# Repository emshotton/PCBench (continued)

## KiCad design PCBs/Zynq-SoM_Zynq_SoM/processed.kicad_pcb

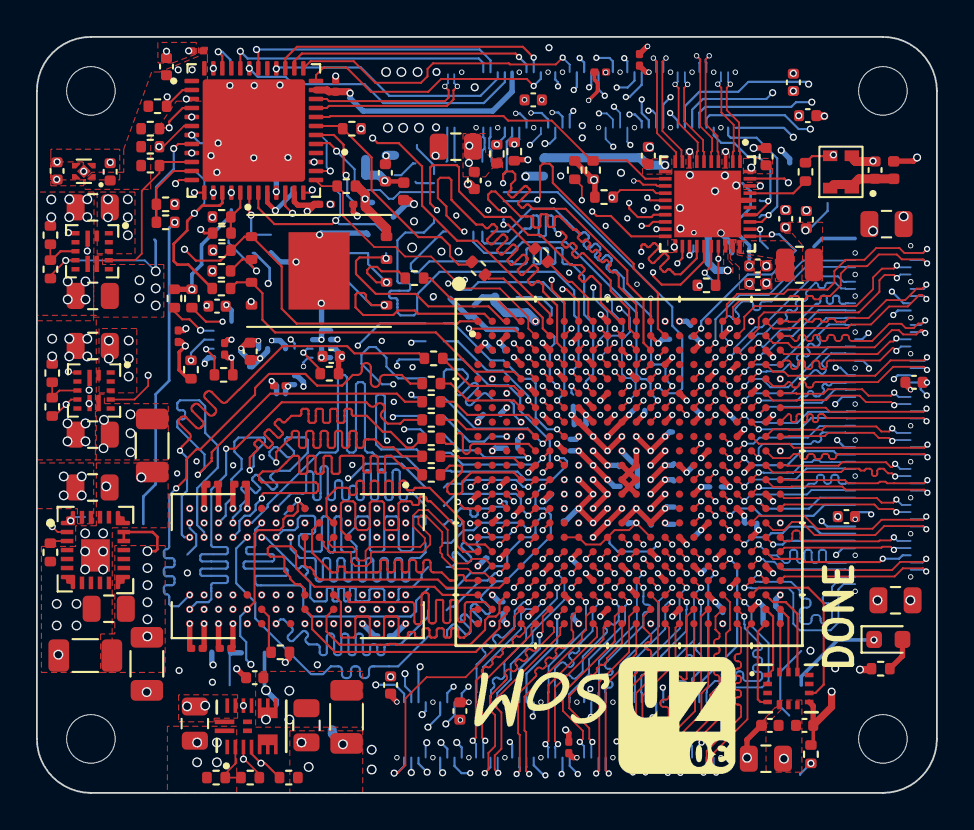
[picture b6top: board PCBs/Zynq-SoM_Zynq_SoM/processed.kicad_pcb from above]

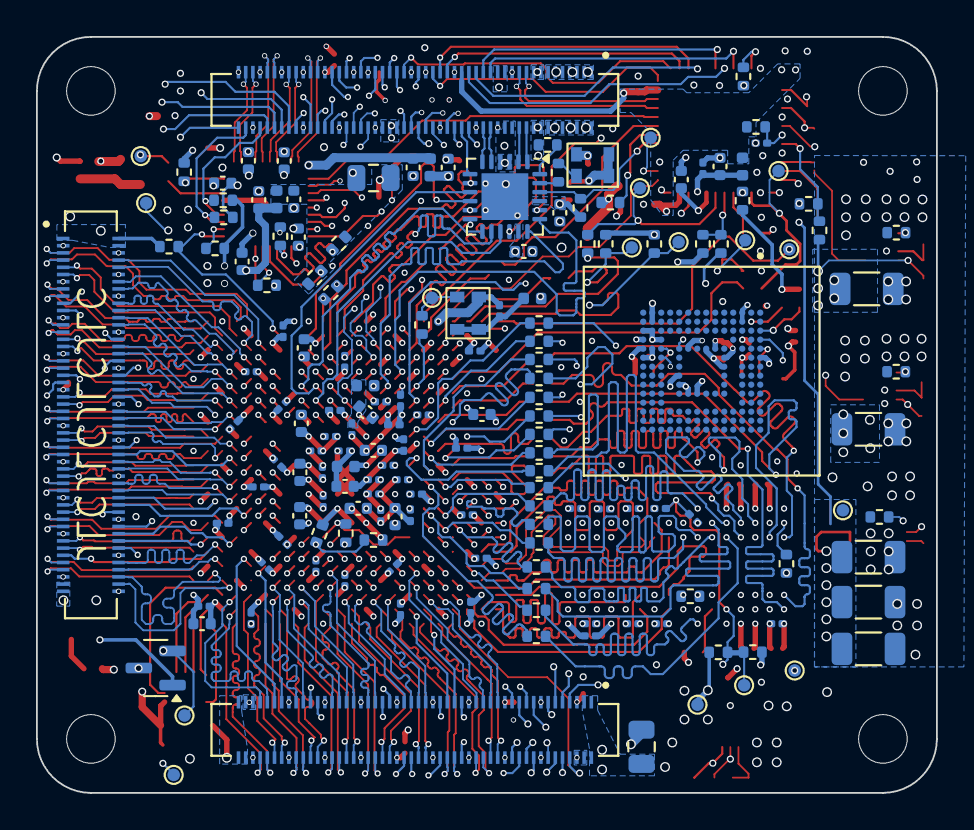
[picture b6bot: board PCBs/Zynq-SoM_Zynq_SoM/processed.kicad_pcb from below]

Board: 8 copper layers, 50.0 x 42.0 mm, 287 parts (166 on the bottom side), 393 nets.

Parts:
C1, C7, C8, C9, C10, C11, C12, C15, C32, C34, C36, C38, C40, C44, C45, C52, C57, C59, C66, C70, C71, C77, C78, C79, C87, C88, C95, C97, C103, C123, C128, C129, C139, C141: 4u7; C_0402_1005Metric
C2, C3, C4, C5, C6, C16, C17, C18, C19, C20, C21, C22, C138, C142: 100n; C_0402_1005Metric
C13, C23, C33, C35, C37, C39, C41, C43, C46, C47, C48, C50, C53, C54, C55, C56, C61, C62, C67, C69, C72, C76, C80, C81, C82, C83, C84, C85, C89, C90, C91, C92, C94, C98, C99, C100, C101, C102, C107, C108, C112, C114, C130, C131, C132, C133, C134, C135, C136, C137: 470n; C_0201_0603Metric
C24, C27, C28, C29, C31, C49, C73, C74, C75, C86, C127: 47u; C_0805_2012Metric
C25, C26, C30: 22u; C_0805_2012Metric
C42, C51, C58, C60, C63, C64, C68, C93, C96: 100u; C_1206_3216Metric
C65: 10u; C_0402_1005Metric
C104, C105, C106, C109, C110, C111, C113, C118, C119, C120, C121, C122, C124, C125, C126: 47n; C_0201_0603Metric
D2: LED_Small; LED_0603_1608Metric
H1, H2, H3, H4: MountingHole; MountingHole_2.7mm_M2.5_ISO14580_MOD
J1, J2, J3: DF40C-100DS-0.4V_51; HRS_DF40C-100DS-0.4V_51_
L1: 3u3; L_0806_2.0x1.6mm
L2, L3, L4, L6, L7, L8, L9: 120R; L_0402_1005Metric
L5: 600@100MHz; L_0402_1005Metric
Q3: NMOS; SOT-23
R1, R5, R6, R13, R15, R39, R40, R41, R42, R43, R44, R74, R75, R76, R77, R86, R87, R88, R89, R90, R92, R93, R94, R97, R100: 10k; R_0402_1005Metric
R2, R20, R21, R22, R49, R51, R52, R53, R54, R55, R56, R57, R58, R59, R60, R61, R62, R63, R64, R65, R66, R67, R68, R69, R70, R71, R72, R73, R95, R96: 22R; R_0402_1005Metric
R3, R4, R14: 1k5; R_0402_1005Metric
R7, R8, R9, R10, R11, R12, R17, R18, R19, R48, R98, R99: 4k7; R_0402_1005Metric
R16: 2k49; R_0402_1005Metric
R23, R27, R28, R29, R30, R31, R32, R35, R36, R78, R79, R80, R81, R82, R83, R84, R85: 100k; R_0402_1005Metric
R24: 8k06; R_0402_1005Metric
R25: 28k7; R_0402_1005Metric
R26, R33, R37: 200k; R_0402_1005Metric
R34: 44k2; R_0402_1005Metric
R38: 160k; R_0402_1005Metric
R45: 240R; R_0402_1005Metric
R46, R47: 100R; R_0201_0603Metric
R50: 100R; R_0402_1005Metric
R91: 330; R_0402_1005Metric
TP1, TP2, TP3, TP4, TP5, TP6, TP7, TP8, TP9, TP10, TP11, TP12, TP13, TP14, TP15, TP16: TestPoint; TestPoint_Pad_D0.7mm
U1: MT41K256M16TW-107_P; BGA96C80P9X16_1400X800X120
U2: XC7Z020-CLG484; CLG484_XIL-L_new
U3: RTL8211F; RTL8211F-CG_RTK-L
U4, U6: MPM3834
U5: USB3318; QFN-24-1EP_4x4mm_P0.5mm_EP2.6x2.6mm
U7: IS21ES08G; BGA153N50P14X14_1150X1300X100
U8: TPSM82864; B0QFN_RDJ
U9: STM32G431CBUx; STM32G431CBU6
U10: MPM3822; QFN_2p5x3p5x1p6_MNP
U11: W25Q128JVS; WSON-8-1EP_8x6mm_P1.27mm_EP3.4x4.3mm
U13: TPS7A20; TLV707
U14: BMI323; BMI323_BOS
X1: ASCO; Oscillator_SMD_Kyocera_4PIN_2.0x1.6mm
X2: ASE-xxxMHz; Oscillator_SMD_Kyocera_4PIN_2.0x1.6mm
X3: CMOS_OSC; Oscillator_SMD_Kyocera_4PIN_2.0x1.6mm

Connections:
1V0_EN: R27.1, U8.1 (EN), U9.5 (PF0)
1V0_PG: R28.2, U8.2 (PG), U9.2 (PC13)
1V8_EN: R30.1, U4.3 (EN), U9.47 (PB9)
1V8_PG: R29.2, U4.11 (PG), U9.4 (PC15)
1V35_EN: R35.1, U9.9 (PA1), U10.4 (EN)
1V35_PG: R36.2, U9.6 (PF1), U10.12 (PG)
3V3_EN: R31.1, U6.3 (EN), U9.3 (PC14)
3V3_PG: R32.2, U6.11 (PG), U9.10 (PA2)
+0V675_REF: C113.2, C124.1, C125.1, C126.1, R88.2, R89.1, TP16.1, U1.H1 (VREFDQ), U1.M8 (VREFCA), U2.H7 (PS_DDR_VREF0_502), U2.P7 (PS_DDR_VREF1_502)
+1V0: C24.1, C45.1, C46.1, C47.1, C48.1, C51.1, C52.1, C53.1, C54.1, C55.1, C56.1, C57.1, C58.1, C60.1, C61.1, C63.1, C64.1, C66.1, R78.1, TP14.1, U2.G8 (VCCPINT), U2.H9 (VCCPINT), U2.H11 (VCCBRAM), U2.J8 (VCCPINT), U2.J10 (VCCBRAM), U2.J12 (VCCINT), U2.J14 (VCCINT), U2.K13 (VCCINT), U2.L8 (VCCPINT), U2.L14 (VCCINT), U2.M13 (VCCINT), U2.N8 (VCCPINT), U2.N14 (VCCINT), U2.P13 (VCCINT), U2.R8 (VCCPINT), U2.R14 (VCCINT), U8.12 (VOUT), U8.13 (VOUT), U8.14 (VOUT), U8.15 (VOUT), U8.16 (VOS), U8.17 (FB)
+1V8: C11.1, C20.1, C27.1, C33.1, C38.1, C42.1, C44.1, C49.1, C50.1, C59.1, C62.1, C67.1, C96.1, C97.1, C98.1, C107.1, C108.1, C112.1, C134.1, C138.1, J1.56, J1.58, J1.60, L2.2, L4.1, L6.2, L8.2, L9.2, R5.1, R7.1, R11.1, R12.1, R14.1, R26.1, R39.1, R40.1, R41.1, R42.1, R43.1, R80.1, R90.1, R92.1, R94.1, R97.1, U2.A10 (VCCO_MIO1_501), U2.B13 (VCCO_MIO1_501), U2.D9 (VCCO_MIO1_501), U2.E12 (VCCO_MIO1_501), U2.G9 (VCCBATT_0), U2.K9 (VCCPAUX), U2.L10 (VCCAUX), U2.M9 (VCCPAUX), U2.N10 (VCCAUX), U2.P9 (VCCPAUX), U2.P11 (VCCAUX), U2.R10 (VCCAUX), U2.T9 (VCCPAUX), U4.6 (OUT_S), U4.9 (OUT), U4.10 (OUT), U5.17 (VDDIO), U5.21 (VDD18), U7.C6 (VCCQ), U7.M4 (VCCQ), U7.N3 (NC), U7.N4 (VCCQ), U7.P3 (VCCQ), U7.P5 (VCCQ)
+1V35: C31.1, C93.1, C95.1, C99.1, C101.1, C102.1, C104.1, C105.1, C106.1, C109.1, C110.1, C111.1, C113.1, C114.1, C118.1, C119.1, C120.1, C121.1, C122.1, C123.1, R37.1, R47.1, R84.1, R88.1, TP15.1, U1.A1 (VDDQ), U1.A8 (VDDQ), U1.B2 (VDD), U1.C1 (VDDQ), U1.C9 (VDDQ), U1.D2 (VDDQ), U1.D9 (VDD), U1.E9 (VDDQ), U1.F1 (VDDQ), U1.G7 (VDD), U1.H2 (VDDQ), U1.H9 (VDDQ), U1.K2 (VDD), U1.K8 (VDD), U1.N1 (VDD), U1.N9 (VDD), U1.R1 (VDD), U1.R9 (VDD), U2.E2 (VCCO_DDR_502), U2.F5 (VCCO_DDR_502), U2.H1 (VCCO_DDR_502), U2.J4 (VCCO_DDR_502), U2.K7 (VCCO_DDR_502), U2.M3 (VCCO_DDR_502), U2.N6 (VCCO_DDR_502), U2.R2 (VCCO_DDR_502), U2.V1 (VCCO_DDR_502), U10.3 (OUT_S), U10.10 (OUT)
+3V3: C1.1, C2.1, C12.1, C21.1, C29.1, C34.1, C39.1, C41.1, C68.1, C71.1, C73.1, C76.1, C141.1, J1.24, J1.25, J1.26, J1.27, L3.1, L7.2, R18.1, R19.1, R33.1, R44.1, R74.2, R82.1, R86.1, R87.1, R91.1, R98.1, R99.1, R100.1, U2.B3 (VCCO_MIO0_500), U2.C6 (VCCO_MIO0_500), U2.R12 (VCCO_0), U2.T7 (VCCO_0), U2.T8 (VCCO_0), U2.T10 (VCCO_0), U2.T13 (CFGBVS_0), U3.29 (DVDD33), U5.3 (VBAT), U5.4 (VDD33), U6.6 (OUT_S), U6.9 (OUT), U6.10 (OUT), U7.E6 (VCC), U7.F5 (VCC), U7.J10 (VCC), U7.K9 (VCC), U11.8 (VCC), U14.8 (VDD)
+3V3_SC: C9.1, C35.1, C36.1, C37.1, C136.1, J1.37, L5.1, R3.1, R28.1, R29.1, R32.1, R36.1, U9.1 (VBAT), U9.23 (VDD), U9.35 (VDD), U9.48 (VDD), U13.1 (OUT)
+VCCO_13: C127.1, C128.1, C129.1, C130.1, C131.1, C132.1, C133.1, J2.1, J2.2, J2.3, U2.AA10 (VCCO_13), U2.AB3 (VCCO_13), U2.T5 (VCCO_13), U2.U8 (VCCO_13), U2.V11 (VCCO_13), U2.W4 (VCCO_13), U2.Y7 (VCCO_13)
+VCCO_33: C86.1, C87.1, C88.1, C89.1, C90.1, C91.1, C92.1, C100.1, J2.98, J2.99, J2.100, U2.AA20 (VCCO_33), U2.AB13 (VCCO_33), U2.U18 (VCCO_33), U2.V21 (VCCO_33), U2.W14 (VCCO_33), U2.Y17 (VCCO_33), U14.5 (VDDIO)
+VCCO_34: C75.1, C77.1, C79.1, C82.1, C83.1, C84.1, C85.1, J3.97, J3.99, U2.K17 (VCCO_34), U2.L20 (VCCO_34), U2.N16 (VCCO_34), U2.P19 (VCCO_34), U2.R22 (VCCO_34), U2.T15 (VCCO_34)
+VCCO_35: C69.1, C70.1, C72.1, C74.1, C78.1, C80.1, C81.1, J3.1, J3.2, J3.4, R15.1, U2.A20 (VCCO_35), U2.C16 (VCCO_35), U2.D19 (VCCO_35), U2.E22 (VCCO_35), U2.F15 (VCCO_35), U2.G18 (VCCO_35), U2.H21 (VCCO_35)
/Ethernet PHY/1V0_ETH: C3.1, C4.1, C5.1, C6.1, C7.1, C16.1, L1.2, TP13.1, U3.3 (AVDD10), U3.8 (AVDD10), U3.21 (DVDD10), U3.38 (AVDD10)
/Ethernet PHY/1V8A_ETH: C10.1, C19.1, L2.1, U3.28 (DVDD_RG)
/Ethernet PHY/3V3A_ETH: C15.1, C17.1, C18.1, L3.2, U3.11 (AVDD33), U3.40 (AVDD33)
/Ethernet PHY/25MHz_1V8: C22.1, L6.1, X2.1 (EN), X2.4 (Vdd)
/Ethernet PHY/CLK_25MHz: R20.1, TP12.1, X2.3 (OUT)
/Ethernet PHY/ETH_CLK_25MHz: R20.2, U3.37 (XTAL_OUT/EXT_CLK)
/Ethernet PHY/ETH_REG_OUT: L1.1, U3.30 (REG_OUT)
/Power/VSET: R25.1, U8.3 (VSET)
/USB HS PHY/13MHz_1V8: C142.1, L8.1, X1.1 (Tri-State), X1.4 (VDD)
/USB HS PHY/CLK_13MHz: R21.1, X1.3 (OUT)
/USB HS PHY/RBIAS: R24.2, U5.24 (RBIAS)
/USB HS PHY/USB_REFCLK: R21.2, U5.23 (REFCLK)
/USB HS PHY/USB_ULPI_CLKOUT_T: R22.1, U5.12 (CLKOUT)
/Zynq B500-B501/33MHz_3V3: C23.1, L7.1, X3.1 (EN), X3.4 (Vdd)
/Zynq B500-B501/PS_CLK_33MHz: R2.1, TP4.1, X3.3 (OUT)
/Zynq B500-B501/PS_CLK_33MHz_T: R2.2, U2.F7 (PS_CLK_500)
/Zynq B500-B501/PS_MIO_VREF_501: C94.1, R92.2, R93.1, U2.F8 (PS_MIO_VREF_501)
/Zynq B500-B501/STM32_SCL_T: R96.2, U2.B6 (PS_MIO14_500)
/Zynq Config/LED_A: D2.2 (A), R91.2
/Zynq Config/VT_OUTPUT: D2.1 (K), Q3.1 (D)
/Zynq Power/VCCADC: C103.1, C135.1, L9.1, U2.K11 (VCCADC_0)
/Zynq Power/VCCPLL: C43.1, C65.1, L4.2, U2.H10 (VCCPLL)
/Zynq_B502_DDR/DDR_A0: R53.1, U2.M4 (PS_DDR_A0_502)
/Zynq_B502_DDR/DDR_A0_T: R53.2, U1.N3 (A0)
/Zynq_B502_DDR/DDR_A1: R54.1, U2.M5 (PS_DDR_A1_502)
/Zynq_B502_DDR/DDR_A1_T: R54.2, U1.P7 (A1)
/Zynq_B502_DDR/DDR_A2: R55.1, U2.K4 (PS_DDR_A2_502)
/Zynq_B502_DDR/DDR_A2_T: R55.2, U1.P3 (A2)
/Zynq_B502_DDR/DDR_A3: R56.1, U2.L4 (PS_DDR_A3_502)
/Zynq_B502_DDR/DDR_A3_T: R56.2, U1.N2 (A3)
/Zynq_B502_DDR/DDR_A4: R57.1, U2.K6 (PS_DDR_A4_502)
/Zynq_B502_DDR/DDR_A4_T: R57.2, U1.P8 (A4)
/Zynq_B502_DDR/DDR_A5: R58.1, U2.K5 (PS_DDR_A5_502)
/Zynq_B502_DDR/DDR_A5_T: R58.2, U1.P2 (A5)
/Zynq_B502_DDR/DDR_A6: R59.1, U2.J7 (PS_DDR_A6_502)
/Zynq_B502_DDR/DDR_A6_T: R59.2, U1.R8 (A6)
/Zynq_B502_DDR/DDR_A7: R60.1, U2.J6 (PS_DDR_A7_502)
/Zynq_B502_DDR/DDR_A7_T: R60.2, U1.R2 (A7)
/Zynq_B502_DDR/DDR_A8: R61.1, U2.J5 (PS_DDR_A8_502)
/Zynq_B502_DDR/DDR_A8_T: R61.2, U1.T8 (A8)
/Zynq_B502_DDR/DDR_A9: R62.1, U2.H5 (PS_DDR_A9_502)
/Zynq_B502_DDR/DDR_A9_T: R62.2, U1.R3 (A9)
/Zynq_B502_DDR/DDR_A10: R63.1, U2.J3 (PS_DDR_A10_502)
/Zynq_B502_DDR/DDR_A10_T: R63.2, U1.L7 (A10/AP)
/Zynq_B502_DDR/DDR_A11: R64.1, U2.G5 (PS_DDR_A11_502)
/Zynq_B502_DDR/DDR_A11_T: R64.2, U1.R7 (A11)
/Zynq_B502_DDR/DDR_A12: R65.1, U2.H4 (PS_DDR_A12_502)
/Zynq_B502_DDR/DDR_A12_T: R65.2, U1.N7 (A12/~BC)
/Zynq_B502_DDR/DDR_A13: R66.1, U2.F4 (PS_DDR_A13_502)
/Zynq_B502_DDR/DDR_A13_T: R66.2, U1.T3 (A13)
/Zynq_B502_DDR/DDR_A14: R67.1, U2.G4 (PS_DDR_A14_502)
/Zynq_B502_DDR/DDR_A14_T: R67.2, U1.T7 (A14)
/Zynq_B502_DDR/DDR_BA0: R68.1, U2.L7 (PS_DDR_BA0_502)
/Zynq_B502_DDR/DDR_BA0_T: R68.2, U1.M2 (BA0)
/Zynq_B502_DDR/DDR_BA1: R69.1, U2.L6 (PS_DDR_BA1_502)
/Zynq_B502_DDR/DDR_BA1_T: R69.2, U1.N8 (BA1)
/Zynq_B502_DDR/DDR_BA2: R70.1, U2.M6 (PS_DDR_BA2_502)
/Zynq_B502_DDR/DDR_BA2_T: R70.2, U1.M3 (BA2)
/Zynq_B502_DDR/DDR_CK_E: R73.1, U2.V3 (PS_DDR_CKE_502)
/Zynq_B502_DDR/DDR_CK_E_T: R73.2, U1.K9 (CKE)
/Zynq_B502_DDR/DDR_CK_N: R50.2, U1.K7 (~CK), U2.N5 (PS_DDR_CKN_502)
/Zynq_B502_DDR/DDR_CK_P: R50.1, U1.J7 (CK), U2.N4 (PS_DDR_CKP_502)
/Zynq_B502_DDR/DDR_DM0: U1.E7 (LDM), U2.AA2 (PS_DDR_DM3_502)
/Zynq_B502_DDR/DDR_DM1: U1.D3 (UDM), U2.P1 (PS_DDR_DM2_502)
/Zynq_B502_DDR/DDR_DQ0: U1.E3 (DQ0), U2.U1 (PS_DDR_DQ25_502)
/Zynq_B502_DDR/DDR_DQ1: U1.F7 (DQ1), U2.AA1 (PS_DDR_DQ26_502)
/Zynq_B502_DDR/DDR_DQ2: U1.F2 (DQ2), U2.U2 (PS_DDR_DQ27_502)
/Zynq_B502_DDR/DDR_DQ3: U1.F8 (DQ3), U2.Y3 (PS_DDR_DQ29_502)
/Zynq_B502_DDR/DDR_DQ4: U1.H3 (DQ4), U2.W3 (PS_DDR_DQ30_502)
/Zynq_B502_DDR/DDR_DQ5: U1.H8 (DQ5), U2.AA3 (PS_DDR_DQ24_502)
/Zynq_B502_DDR/DDR_DQ6: U1.G2 (DQ6), U2.W1 (PS_DDR_DQ28_502)
/Zynq_B502_DDR/DDR_DQ7: U1.H7 (DQ7), U2.Y1 (PS_DDR_DQ31_502)
/Zynq_B502_DDR/DDR_DQ8: U1.D7 (DQ8), U2.R3 (PS_DDR_DQ20_502)
/Zynq_B502_DDR/DDR_DQ9: U1.C3 (DQ9), U2.N3 (PS_DDR_DQ18_502)
/Zynq_B502_DDR/DDR_DQ10: U1.C8 (DQ10), U2.T2 (PS_DDR_DQ21_502)
/Zynq_B502_DDR/DDR_DQ11: U1.C2 (DQ11), U2.M2 (PS_DDR_DQ22_502)
/Zynq_B502_DDR/DDR_DQ12: U1.A7 (DQ12), U2.R1 (PS_DDR_DQ23_502)
/Zynq_B502_DDR/DDR_DQ13: U1.A2 (DQ13), U2.M1 (PS_DDR_DQ16_502)
/Zynq_B502_DDR/DDR_DQ14: U1.B8 (DQ14), U2.T1 (PS_DDR_DQ19_502)
/Zynq_B502_DDR/DDR_DQ15: U1.A3 (DQ15), U2.T3 (PS_DDR_DQ17_502)
/Zynq_B502_DDR/DDR_DQS0_N: U1.G3 (~LDQS), U2.W2 (PS_DDR_DQS_N3_502)
/Zynq_B502_DDR/DDR_DQS0_P: U1.F3 (LDQS), U2.V2 (PS_DDR_DQS_P3_502)
/Zynq_B502_DDR/DDR_DQS1_N: U1.B7 (~UDQS), U2.P2 (PS_DDR_DQS_N2_502)
/Zynq_B502_DDR/DDR_DQS1_P: U1.C7 (UDQS), U2.N2 (PS_DDR_DQS_P2_502)
/Zynq_B502_DDR/DDR_ODT: R72.1, U2.P5 (PS_DDR_ODT_502)
/Zynq_B502_DDR/DDR_ODT_T: R72.2, U1.K1 (ODT)
/Zynq_B502_DDR/DDR_VRN: R46.1, U2.M7 (PS_DDR_VRN_502)
/Zynq_B502_DDR/DDR_VRP: R47.2, U2.N7 (PS_DDR_VRP_502)
/Zynq_B502_DDR/DDR_ZQ: R45.1, U1.L8 (ZQ)
/Zynq_B502_DDR/DDR_~CAS: R49.1, U2.P3 (PS_DDR_CAS_B_502)
/Zynq_B502_DDR/DDR_~CAS_T: R49.2, U1.K3 (~CAS)
/Zynq_B502_DDR/DDR_~CS: R51.1, U2.P6 (PS_DDR_CS_B_502)
/Zynq_B502_DDR/DDR_~CS_T: R51.2, U1.L2 (~CS)
/Zynq_B502_DDR/DDR_~RAS: R52.1, U2.R5 (PS_DDR_RAS_B_502)
/Zynq_B502_DDR/DDR_~RAS_T: R52.2, U1.J3 (~RAS)
/Zynq_B502_DDR/DDR_~RST: R48.1, U1.T2 (~RESET), U2.F3 (PS_DDR_DRST_B_502)
/Zynq_B502_DDR/DDR_~WE: R71.1, U2.R4 (PS_DDR_WE_B_502)
/Zynq_B502_DDR/DDR_~WE_T: R71.2, U1.L3 (~WE)
/eMMC/eMMC_VDDI: C40.1, U7.C1 (NC), U7.C2 (VDDI)
ETH_LED0: R18.2, U3.32 (LED0/CFG_EXT)
ETH_LED1: J1.98, R17.1, U3.33 (LED1/CFG_LDO0)
ETH_LED2: J1.94, R19.2, U3.34 (LED2/CFG_LDO1)
ETH_PHY_INT: R15.2, U2.B16 (IO_L8P_T1_AD10P_35), U3.31 (INT/PMEB)
ETH_PHY_MDC: U2.D10 (PS_MIO52_501), U3.13 (MDC)
ETH_PHY_MDI0_N: J1.95, U3.2 (MDIN0)
ETH_PHY_MDI0_P: J1.97, U3.1 (MDIP0)
ETH_PHY_MDI1_N: J1.89, U3.5 (MDIN1)
ETH_PHY_MDI1_P: J1.91, U3.4 (MDIP1)
ETH_PHY_MDI2_N: J1.83, U3.7 (MDIN2)
ETH_PHY_MDI2_P: J1.85, U3.6 (MDIP2)
ETH_PHY_MDI3_N: J1.77, U3.10 (MDIN3)
ETH_PHY_MDI3_P: J1.79, U3.9 (MDIP3)
ETH_PHY_MDIO: R14.2, U2.C12 (PS_MIO53_501), U3.14 (MDIO)
ETH_PHY_RST: R90.2, U3.12 (PHYRSTB), U9.32 (PA10)
ETH_PHY_RXC: R9.1, U2.A14 (PS_MIO22_501), U3.27 (RXC/PHYAD1)
ETH_PHY_RXCTL: R10.1, U2.D7 (PS_MIO27_501), U3.26 (RXCTL/PHYAD2)
ETH_PHY_RXD0: R12.2, U2.E11 (PS_MIO23_501), U3.25 (RXD0/RXDLY)
ETH_PHY_RXD1: R11.2, U2.B7 (PS_MIO24_501), U3.24 (RXD1/TXDLY)
ETH_PHY_RXD2: R8.1, U2.F12 (PS_MIO25_501), U3.23 (RXD2/PLLOFF)
ETH_PHY_RXD3: R7.2, U2.A13 (PS_MIO26_501), U3.22 (RXD3/PHYAD0)
ETH_PHY_TXC: U2.D6 (PS_MIO16_501), U3.20 (TXC)
ETH_PHY_TXCTL: U2.F11 (PS_MIO21_501), U3.19 (TXCTL)
ETH_PHY_TXD0: U2.E9 (PS_MIO17_501), U3.18 (TXD0)
ETH_PHY_TXD1: U2.A7 (PS_MIO18_501), U3.17 (TXD1)
ETH_PHY_TXD2: U2.E10 (PS_MIO19_501), U3.16 (TXD2)
ETH_PHY_TXD3: U2.A8 (PS_MIO20_501), U3.15 (TXD3)
GND: C1.2, C2.2, C3.2, C4.2, C5.2, C6.2, C7.2, C8.2, C9.2, C10.2, C11.2, C12.2, C13.2, C15.2, C16.2, C17.2, C18.2, C19.2, C20.2, C21.2, C22.2, C23.2, C24.2, C25.2, C26.2, C27.2, C28.2, C29.2, C30.2, C31.2, C32.2, C33.2, C34.2, C35.2, C36.2, C37.2, C38.2, C39.2, C40.2, C41.2, C42.2, C43.2, C44.2, C45.2, C46.2, C47.2, C48.2, C49.2, C50.2, C51.2, C52.2, C53.2, C54.2, C55.2, C56.2, C57.2, C58.2, C59.2, C60.2, C61.2, C62.2, C63.2, C64.2, C65.2, C66.2, C67.2, C68.2, C69.2, C70.2, C71.2, C72.2, C73.2, C74.2, C75.2, C76.2, C77.2, C78.2, C79.2, C80.2, C81.2, C82.2, C83.2, C84.2, C85.2, C86.2, C87.2, C88.2, C89.2, C90.2, C91.2, C92.2, C93.2, C94.2, C95.2, C96.2, C97.2, C98.2, C99.2, C100.2, C101.2, C102.2, C103.2, C104.2, C105.2, C106.2, C107.2, C108.2, C109.2, C110.2, C111.2, C112.2, C114.2, C118.2, C119.2, C120.2, C121.2, C122.2, C123.2, C124.2, C125.2, C126.2, C127.2, C128.2, C129.2, C130.2, C131.2, C132.2, C133.2, C134.2, C135.2, C136.2, C137.2, C138.2, C139.2, C141.2, C142.2, J1.15, J1.16, J1.17, J1.18, J1.23, J1.28, J1.34, J1.39, J1.44, J1.51, J1.62, J1.63, J1.72, J1.75, J1.81, J1.82, J1.87, J1.93, J1.96, J1.99, J2.4, J2.5, J2.6, J2.15, J2.16, J2.25, J2.26, J2.35, J2.36, J2.45, J2.46, J2.55, J2.56, J2.65, J2.66, J2.75, J2.76, J2.85, J2.86, J2.95, J2.96, J2.97, J3.3, J3.6, J3.12, J3.13, J3.18, J3.23, J3.28, J3.33, J3.38, J3.43, J3.48, J3.53, J3.58, J3.63, J3.68, J3.73, J3.80, J3.83, J3.90, J3.95, J3.100, Q3.3 (S), R4.2, R8.2, R9.2, R10.2, R13.2, R16.2, R17.2, R23.2, R24.1, R25.2, R27.2, R30.2, R31.2, R34.2, R35.2, R38.2, R45.2, R46.2, R48.2, R75.1, R76.2, R77.2, R79.2, R81.2, R83.2, R85.2, R89.2, R93.2, U1.A9 (VSS), U1.B1 (VSSQ), U1.B3 (VSS), U1.B9 (VSSQ), U1.D1 (VSSQ), U1.D8 (VSSQ), U1.E1 (VSS), U1.E2 (VSSQ), U1.E8 (VSSQ), U1.F9 (VSSQ), U1.G1 (VSSQ), U1.G8 (VSS), U1.G9 (VSSQ), U1.J2 (VSS), U1.J8 (VSS), U1.M1 (VSS), U1.M9 (VSS), U1.P1 (VSS), U1.P9 (VSS), U1.T1 (VSS), U1.T9 (VSS), U2.A5 (GND), U2.A15 (GND), U2.AA5 (GND), U2.AA15 (GND), U2.AB8 (GND), U2.AB18 (GND), U2.B8 (GND), U2.B18 (GND), U2.C1 (GND), U2.C11 (GND), U2.C21 (GND), U2.D4 (GND), U2.D14 (GND), U2.E7 (GND), U2.E17 (GND), U2.F10 (GND), U2.F20 (GND), U2.G3 (GND), U2.H6 (GND), U2.H8 (GND), U2.H12 (GND), U2.H14 (GND), U2.H16 (GND), U2.J9 (GND), U2.J11 (GND), U2.J13 (GND), U2.J19 (GND), U2.K2 (GND), U2.K8 (GND), U2.K10 (GND), U2.K12 (GNDADC_0), U2.K14 (GND), U2.K22 (GND), U2.L5 (GND), U2.L9 (GND), U2.L11 (VP_0), U2.L12 (VREFN_0), U2.L13 (GND), U2.L15 (GND), U2.M8 (GND), U2.M10 (GND), U2.M11 (VREFP_0), U2.M12 (VN_0), U2.M14 (GND), U2.M18 (GND), U2.N1 (GND), U2.N9 (GND), U2.N11 (DXP_0), U2.N12 (DXN_0), U2.N13 (GND), U2.N21 (GND), U2.P4 (GND), U2.P8 (GND), U2.P10 (GND), U2.P12 (GND), U2.P14 (GND), U2.R9 (GND), U2.R11 (GND), U2.R13 (GND), U2.R17 (GND), U2.T20 (GND), U2.U3 (GND), U2.U13 (GND), U2.V6 (GND), U2.V16 (GND), U2.W9 (GND), U2.W19 (GND), U2.Y2 (GND), U2.Y12 (GND), U2.Y22 (GND), U3.36 (XTAL_IN), U3.41 (GND), U4.2 (PGND), U4.4 (AGND), U4.7 (PGND), U4.8 (PGND), U5.25 (GND), U6.2 (PGND), U6.4 (AGND), U6.7 (PGND), U6.8 (PGND), U7.A6 (VSS), U7.C4 (VSSQ), U7.E7 (VSS), U7.G5 (VSS), U7.H10 (VSS), U7.J5 (VSS), U7.K8 (VSS), U7.N1 (NC), U7.N2 (VSSQ), U7.N5 (VSSQ), U7.N6 (NC), U7.P4 (VSSQ), U7.P6 (VSSQ), U8.4 (PGND), U8.5 (PGND), U8.6 (PGND), U8.8 (PGND), U8.9 (PGND), U8.10 (PGND), U8.11 (PGND), U8.18 (AGND), U8.19 (PGND), U8.20 (PGND), U8.23 (PGND), U9.49 (VSS), U10.1 (AGND), U10.16 (PGND), U11.4 (GND), U11.9 (PAD), U13.2 (GND), U13.5 (PAD), U14.6 (GNDIO), U14.7 (GND), X1.2 (GND), X2.2 (GND), X3.2 (GND)
IO_0_35: J1.86, U2.H17 (IO_0_35)
IO_25_13: J2.23, U2.U7 (IO_25_13)
IO_25_33: J2.79, U2.U14 (IO_25_33)
IO_L1P_13: J2.57, U2.V10 (IO_L1P_T0_13)
IO_L1_N_13: J2.37, U2.V9 (IO_L1N_T0_13)
IO_L1_N_33: J3.89, U2.U21 (IO_L1N_T0_33)
IO_L1_N_35: J1.92, U2.E16 (IO_L1N_T0_AD0N_35)
IO_L1_P_33: J3.86, U2.T21 (IO_L1P_T0_33)
IO_L1_P_35: J1.74, U2.F16 (IO_L1P_T0_AD0P_35)
IO_L2_N_13: J2.14, U2.W8 (IO_L2N_T0_13)
IO_L2_N_33: J3.87, U2.U22 (IO_L2N_T0_33)
IO_L2_N_35: J1.100, U2.D17 (IO_L2N_T0_AD8N_35)
IO_L2_P_13: J2.20, U2.V8 (IO_L2P_T0_13)
IO_L2_P_33: J3.85, U2.T22 (IO_L2P_T0_33)
IO_L3P_PUDC_34: J3.39, U2.K16 (IO_L3P_T0_DQS_PUDC_B_34)
IO_L3_DQS_N_33: J3.93, U2.W22 (IO_L3N_T0_DQS_33)
IO_L3_DQS_P_33: J3.91, U2.V22 (IO_L3P_T0_DQS_33)
IO_L3_N_13: J2.43, U2.W10 (IO_L3N_T0_DQS_13)
IO_L3_P_13: J2.18, U2.W11 (IO_L3P_T0_DQS_13)
IO_L4_N_13: J2.63, U2.W12 (IO_L4N_T0_13)
IO_L4_N_33: J3.96, U2.W21 (IO_L4N_T0_33)
IO_L4_N_34: J3.41, U2.M17 (IO_L4N_T0_34)
IO_L4_N_35: J1.84, U2.G16 (IO_L4N_T0_35)
IO_L4_P_13: J2.61, U2.V12 (IO_L4P_T0_13)
IO_L4_P_33: J3.98, U2.W20 (IO_L4P_T0_33)
IO_L4_P_35: J1.80, U2.G15 (IO_L4P_T0_35)
IO_L5P_13: J2.38, U2.U12 (IO_L5P_T0_13)
IO_L5_N_13: J2.24, U2.U11 (IO_L5N_T0_13)
IO_L5_N_33: J3.94, U2.V20 (IO_L5N_T0_33)
IO_L5_N_34: J3.36, U2.N18 (IO_L5N_T0_34)
IO_L5_N_35: J1.88, U2.E18 (IO_L5N_T0_AD9N_35)
IO_L5_P_33: J3.92, U2.U20 (IO_L5P_T0_33)
IO_L5_P_34: J3.60, U2.N17 (IO_L5P_T0_34)
IO_L5_P_35: J1.90, U2.F18 (IO_L5P_T0_AD9P_35)
IO_L6_N_VREF_13: J2.17, U2.U9 (IO_L6N_T0_VREF_13)
IO_L6_P_13: J2.21, U2.U10 (IO_L6P_T0_13)
IO_L6_P_33: J2.89, U2.V18 (IO_L6P_T0_33)
IO_L6_P_35: J1.78, U2.G17 (IO_L6P_T0_35)
IO_L6_VREF_N_34: J3.78, U2.M16 (IO_L6N_T0_VREF_34)
IO_L6_VREF_N_35: J1.76, U2.F17 (IO_L6N_T0_VREF_35)
IO_L7_N_13: J2.64, U2.AB12 (IO_L7N_T1_13)
IO_L7_N_33: U2.AB22 (IO_L7N_T1_33), U14.14 (SDX)
IO_L7_N_34: J3.40, U2.K18 (IO_L7N_T1_34)
IO_L7_P_13: J2.62, U2.AA12 (IO_L7P_T1_13)
IO_L7_P_33: U2.AA22 (IO_L7P_T1_33), U14.13 (SCX)
IO_L7_P_34: J3.19, U2.J18 (IO_L7P_T1_34)
IO_L8_N_13: J2.60, U2.AB11 (IO_L8N_T1_13)
IO_L8_N_33: U2.AB21 (IO_L8N_T1_33), U14.4 (INT1)
IO_L8_N_34: J3.57, U2.J22 (IO_L8N_T1_34)
IO_L8_P_13: J2.58, U2.AA11 (IO_L8P_T1_13)
IO_L8_P_33: U2.AA21 (IO_L8P_T1_33), U14.1 (SDO)
IO_L8_P_34: J3.55, U2.J21 (IO_L8P_T1_34)
IO_L9_DQS_N_13: J2.48, U2.AB9 (IO_L9N_T1_DQS_13)
IO_L9_DQS_N_33: U2.Y21 (IO_L9N_T1_DQS_33), U14.12 (CSB)
IO_L9_DQS_N_34: J3.61, U2.K21 (IO_L9N_T1_DQS_34)
IO_L9_DQS_P_13: J2.50, U2.AB10 (IO_L9P_T1_DQS_13)
IO_L9_DQS_P_33: U2.Y20 (IO_L9P_T1_DQS_33), U14.9 (INT2)
IO_L9_DQS_P_34: J3.59, U2.J20 (IO_L9P_T1_DQS_34)
IO_L10_N_13: J2.51, U2.Y10 (IO_L10N_T1_13)
IO_L10_N_33: J2.94, U2.AB20 (IO_L10N_T1_33)
IO_L10_N_34: J3.65, U2.L22 (IO_L10N_T1_34)
IO_L10_N_35: J3.7, U2.A19 (IO_L10N_T1_AD11N_35)
IO_L10_P_13: J2.53, U2.Y11 (IO_L10P_T1_13)
IO_L10_P_33: J2.92, U2.AB19 (IO_L10P_T1_33)
IO_L10_P_34: J3.67, U2.L21 (IO_L10P_T1_34)
IO_L10_P_35: J3.5, U2.A18 (IO_L10P_T1_AD11P_35)
IO_L11_SRCC_N_13: J2.40, U2.AA8 (IO_L11N_T1_SRCC_13)
IO_L11_SRCC_N_33: J2.91, U2.AA19 (IO_L11N_T1_SRCC_33)
IO_L11_SRCC_N_34: J3.56, U2.K20 (IO_L11N_T1_SRCC_34)
IO_L11_SRCC_N_35: J3.10, U2.C18 (IO_L11N_T1_SRCC_35)
IO_L11_SRCC_P_13: J2.42, U2.AA9 (IO_L11P_T1_SRCC_13)
IO_L11_SRCC_P_33: J2.93, U2.Y19 (IO_L11P_T1_SRCC_33)
IO_L11_SRCC_P_34: J3.54, U2.K19 (IO_L11P_T1_SRCC_34)
IO_L11_SRCC_P_35: J3.8, U2.C17 (IO_L11P_T1_SRCC_35)
IO_L12_MRCC_N_13: J2.47, U2.Y8 (IO_L12N_T1_MRCC_13)
IO_L12_MRCC_N_33: J2.88, U2.AA18 (IO_L12N_T1_MRCC_33)
IO_L12_MRCC_N_34: J3.62, U2.L19 (IO_L12N_T1_MRCC_34)
IO_L12_MRCC_N_35: J3.16, U2.C19 (IO_L12N_T1_MRCC_35)
IO_L12_MRCC_P_13: J2.49, U2.Y9 (IO_L12P_T1_MRCC_13)
IO_L12_MRCC_P_33: J2.90, U2.Y18 (IO_L12P_T1_MRCC_33)
IO_L12_MRCC_P_34: J3.46, U2.L18 (IO_L12P_T1_MRCC_34)
IO_L12_MRCC_P_35: J3.14, U2.D18 (IO_L12P_T1_MRCC_35)
IO_L13_MRCC_N_13: J2.27, U2.Y5 (IO_L13N_T2_MRCC_13)
IO_L13_MRCC_N_34: J3.64, U2.M20 (IO_L13N_T2_MRCC_34)
IO_L13_MRCC_N_35: J3.11, U2.B20 (IO_L13N_T2_MRCC_35)
IO_L13_MRCC_P_13: J2.29, U2.Y6 (IO_L13P_T2_MRCC_13)
IO_L13_MRCC_P_34: J3.66, U2.M19 (IO_L13P_T2_MRCC_34)
IO_L13_MRCC_P_35: J3.9, U2.B19 (IO_L13P_T2_MRCC_35)
IO_L14_N_SRCC_13: J2.39, U2.AA6 (IO_L14N_T2_SRCC_13)
IO_L14_P_SRCC_13: J2.41, U2.AA7 (IO_L14P_T2_SRCC_13)
IO_L14_SRCC_N_33: J2.83, U2.Y16 (IO_L14N_T2_SRCC_33)
IO_L14_SRCC_N_34: J3.70, U2.N20 (IO_L14N_T2_SRCC_34)
IO_L14_SRCC_N_35: J3.20, U2.C20 (IO_L14N_T2_AD4N_SRCC_35)
IO_L14_SRCC_P_33: J2.81, U2.W16 (IO_L14P_T2_SRCC_33)
IO_L14_SRCC_P_34: J3.72, U2.N19 (IO_L14P_T2_SRCC_34)
IO_L14_SRCC_P_35: J3.22, U2.D20 (IO_L14P_T2_AD4P_SRCC_35)
IO_L15_DQS_N_34: J3.69, U2.M22 (IO_L15N_T2_DQS_34)
IO_L15_DQS_N_35: J3.15, U2.A22 (IO_L15N_T2_DQS_AD12N_35)
IO_L15_DQS_P_34: J3.71, U2.M21 (IO_L15P_T2_DQS_34)
IO_L15_DQS_P_35: J3.17, U2.A21 (IO_L15P_T2_DQS_AD12P_35)
IO_L15_N_33: J2.54, U2.U16 (IO_L15N_T2_DQS_33)
IO_L15_P_13: J2.9, U2.AB2 (IO_L15P_T2_DQS_13)
IO_L15_P_33: J2.77, U2.V15 (IO_L19N_T3_VREF_33)
IO_L16_N_13: J2.28, U2.AB4 (IO_L16N_T2_13)
IO_L16_N_33: J2.87, U2.V17 (IO_L16N_T2_33)
IO_L16_N_34: J3.77, U2.P22 (IO_L16N_T2_34)
IO_L16_N_35: J3.29, U2.C22 (IO_L16N_T2_35)
IO_L16_P_13: J2.30, U2.AB5 (IO_L16P_T2_13)
IO_L16_P_34: J3.75, U2.N22 (IO_L16P_T2_34)
IO_L16_P_35: J3.31, U2.D22 (IO_L16P_T2_35)
IO_L17_N_13: J2.32, U2.AB6 (IO_L17N_T2_13)
IO_L17_N_33: J2.84, U2.AB17 (IO_L17N_T2_33)
IO_L17_N_34: J3.81, U2.R21 (IO_L17N_T2_34)
IO_L17_N_35: J3.35, U2.D21 (IO_L17N_T2_AD5N_35)
IO_L17_P_13: J2.34, U2.AB7 (IO_L17P_T2_13)
IO_L17_P_33: J2.82, U2.AA17 (IO_L17P_T2_33)
IO_L17_P_34: J3.79, U2.R20 (IO_L17P_T2_34)
IO_L17_P_35: J3.37, U2.E21 (IO_L17P_T2_AD5P_35)
IO_L18_N_13: J2.8, U2.AA4 (IO_L18N_T2_13)
IO_L18_N_33: J2.80, U2.AB16 (IO_L18N_T2_33)
IO_L18_N_34: J3.74, U2.P21 (IO_L18N_T2_34)
IO_L18_N_35: J3.25, U2.B22 (IO_L18N_T2_AD13N_35)
IO_L18_P_13: J2.11, U2.Y4 (IO_L18P_T2_13)
IO_L18_P_33: J2.78, U2.AA16 (IO_L18P_T2_33)
IO_L18_P_35: J3.27, U2.B21 (IO_L18P_T2_AD13P_35)
IO_L19_N_VREF_35: J3.52, U2.H20 (IO_L19N_T3_VREF_35)
IO_L19_P_13: J2.12, U2.R6 (IO_L19P_T3_13)
IO_L19_P_33: J2.22, U2.V14 (IO_L19P_T3_33)
IO_L19_P_35: J3.50, U2.H19 (IO_L19P_T3_35)
IO_L19_VREF_N_33: J2.52, U2.U15 (IO_L15P_T2_DQS_33)
IO_L20_N_33: J2.44, U2.W13 (IO_L20N_T3_33)
IO_L20_N_34: J3.76, U2.P18 (IO_L20N_T3_34)
IO_L20_N_35: J3.32, U2.F19 (IO_L20N_T3_AD6N_35)
IO_L20_P_33: J2.59, U2.V13 (IO_L20P_T3_33)
IO_L20_P_34: J3.30, U2.P17 (IO_L20P_T3_34)
IO_L20_P_35: J3.34, U2.G19 (IO_L20P_T3_AD6P_35)
IO_L21_DQS_N_33: J2.73, U2.Y15 (IO_L21N_T3_DQS_33)
IO_L21_DQS_N_35: J3.26, U2.E20 (IO_L21N_T3_DQS_AD14N_35)
IO_L21_DQS_P_33: J2.71, U2.W15 (IO_L21P_T3_DQS_33)
IO_L21_DQS_P_35: J3.24, U2.E19 (IO_L21P_T3_DQS_AD14P_35)
IO_L21_P_13: J2.13, U2.V5 (IO_L21P_T3_DQS_13)
IO_L22_N_33: J2.69, U2.AA14 (IO_L22N_T3_33)
IO_L22_N_34: J3.84, U2.T19 (IO_L22N_T3_34)
IO_L22_N_35: J3.44, U2.G21 (IO_L22N_T3_AD7N_35)
IO_L22_P_13: J2.19, U2.U6 (IO_L22P_T3_13)
IO_L22_P_33: J2.67, U2.Y14 (IO_L22P_T3_33)
IO_L22_P_35: J3.42, U2.G20 (IO_L22P_T3_AD7P_35)
IO_L23_N_13: J2.31, U2.W7 (IO_L23N_T3_13)
IO_L23_N_33: J2.68, U2.AA13 (IO_L23N_T3_33)
IO_L23_N_35: J3.45, U2.F22 (IO_L23N_T3_35)
IO_L23_P_13: J2.33, U2.V7 (IO_L23P_T3_13)
IO_L23_P_33: J2.70, U2.Y13 (IO_L23P_T3_33)
IO_L23_P_34: J3.88, U2.R18 (IO_L23P_T3_34)
IO_L23_P_35: J3.47, U2.F21 (IO_L23P_T3_35)
IO_L24_N_13: J2.7, U2.W5 (IO_L24N_T3_13)
IO_L24_N_33: J2.74, U2.AB15 (IO_L24N_T3_33)
IO_L24_N_34: J3.21, U2.R16 (IO_L24N_T3_34)
IO_L24_N_35: J3.49, U2.G22 (IO_L24N_T3_AD15N_35)
IO_L24_P_13: J2.10, U2.W6 (IO_L24P_T3_13)
IO_L24_P_33: J2.72, U2.AB14 (IO_L24P_T3_33)
IO_L24_P_34: J3.82, U2.P16 (IO_L24P_T3_34)
IO_L24_P_35: J3.51, U2.H22 (IO_L24P_T3_AD15P_35)
unnamed: R16.1, U3.39 (RSET)
unnamed: R23.1, R26.2, U4.5 (FB)
unnamed: R33.2, R34.1, U6.5 (FB)
unnamed: C32.1, C137.1, L5.2, U9.21 (VDDA)
unnamed: C139.1, U9.20 (VREF+)
unnamed: R37.2, R38.1, U10.2 (FB)
QSPI_CLK: R13.1, R95.1, TP11.1, U11.6 (CLK)
QSPI_CLK_T/BM4: R95.2, U2.A4 (PS_MIO6_500)
QSPI_D0/BM3: R76.1, TP7.1, U2.A2 (PS_MIO2_500), U11.5 (DI(IO0))
QSPI_D1/BM1: R77.1, TP8.1, U2.F6 (PS_MIO3_500), U11.2 (DO(IO1))
QSPI_D2/BM2: R1.2, U2.E4 (PS_MIO4_500), U11.3 (IO2)
QSPI_D3/BM0: R6.2, U2.A3 (PS_MIO5_500), U11.7 (IO3)
QSPI_~CS: R44.2, TP6.1, U2.A1 (PS_MIO1_500), U11.1 (~CS)
SDIO_CLK: J1.67, U2.E14 (PS_MIO40_501)
SDIO_CMD: J1.69, U2.C8 (PS_MIO41_501)
SDIO_D0: J1.65, U2.D8 (PS_MIO42_501)
SDIO_D1: J1.61, U2.B11 (PS_MIO43_501)
SDIO_D2: J1.73, U2.E13 (PS_MIO44_501)
SDIO_D3: J1.71, U2.B9 (PS_MIO45_501)
SENSE_1V0: R78.2, R79.1, U9.11 (PA3)
SENSE_1V8: R80.2, R81.1, U9.18 (PB1)
SENSE_1V35: R84.2, R85.1, U9.17 (PB0)
SENSE_3V3: R82.2, R83.1, U9.8 (PA0)
STM32_BOOT0: J1.57, R4.1, U9.46 (PB8)
STM32_DAC1: J1.49, U9.12 (PA4)
STM32_DAC2: J1.55, U9.13 (PA5)
STM32_GPIO1: J1.33, U9.40 (PC11)
STM32_GPIO2: J1.35, U9.43 (PB5)
STM32_GPIO3: J1.43, U9.39 (PC10)
STM32_GPIO4: J1.41, U9.38 (PA15)
STM32_GPIO5: J1.53, U9.37 (PA14)
STM32_GPIO6: J1.45, U9.36 (PA13)
STM32_GPIO7: J1.59, U9.22 (PB10)
STM32_GPIO8: J1.54, U9.24 (PB11)
STM32_NRST: C13.1, J1.47, R3.2, U9.7 (PG10)
STM32_SCL: R86.2, R96.1, U9.31 (PA9)
STM32_SDA: R87.2, U2.E6 (PS_MIO15_500), U9.30 (PA8)
STM32_USB_CC1: J1.29, U9.44 (PB6)
STM32_USB_CC2: J1.31, U9.42 (PB4)
STM32_USB_D_N: J1.21, U9.33 (PA11)
STM32_USB_D_P: J1.19, U9.34 (PA12)
USB_D+: J1.32, U5.6 (DP)
USB_D-: J1.30, U5.5 (DM)
USB_ID: J1.20, U5.1 (ID)
USB_PHY_RST: R5.2, U5.22 (~RESETB), U9.29 (PC6)
USB_ULPI_CLKOUT: R22.2, U2.A9 (PS_MIO36_501)
USB_ULPI_DATA0: U2.C7 (PS_MIO32_501), U5.16 (DATA0)
USB_ULPI_DATA1: U2.G13 (PS_MIO33_501), U5.15 (DATA1)
USB_ULPI_DATA2: U2.B12 (PS_MIO34_501), U5.14 (DATA2)
USB_ULPI_DATA3: U2.F14 (PS_MIO35_501), U5.13 (DATA3)
USB_ULPI_DATA4: U2.A12 (PS_MIO28_501), U5.11 (DATA4)
USB_ULPI_DATA5: U2.B14 (PS_MIO37_501), U5.10 (DATA5)
USB_ULPI_DATA6: U2.F13 (PS_MIO38_501), U5.9 (DATA6)
USB_ULPI_DATA7: U2.C13 (PS_MIO39_501), U5.8 (DATA7)
USB_ULPI_DIR: U2.E8 (PS_MIO29_501), U5.19 (DIR)
USB_ULPI_NXT: U2.F9 (PS_MIO31_501), U5.18 (NXT)
USB_ULPI_STP: U2.A11 (PS_MIO30_501), U5.20 (STP)
USB_VBUS: J1.22, U5.2 (VBUS)
VBUS_OUT_EN: J1.38, U5.7 (CPEN)
VIN: C8.1, C25.1, C26.1, C28.1, C30.1, J1.1, J1.2, J1.3, J1.4, J1.5, J1.6, J1.7, J1.8, J1.9, J1.10, J1.11, J1.12, J1.13, J1.14, U4.12 (VIN), U4.13 (VIN), U4.14 (VIN), U6.12 (VIN), U6.13 (VIN), U6.14 (VIN), U8.21 (VIN), U8.22 (VIN), U10.13 (VIN), U10.14 (VIN), U13.3 (EN), U13.4 (IN)
ZYNQ_BMODE_0: R6.1, TP10.1, U9.19 (PB2)
ZYNQ_BMODE_2: R1.1, TP9.1, U9.15 (PA7)
ZYNQ_PL_DONE: Q3.2 (G), TP3.1, U2.T12 (DONE_0)
ZYNQ_PL_INITB: R99.2, TP2.1, U2.T14 (INIT_B_0)
ZYNQ_PL_PROGB: R98.2, TP1.1, U2.T11 (PROGRAM_B_0), U9.14 (PA6)
ZYNQ_PS_MIO0: J1.50, U2.G6 (PS_MIO0_500)
ZYNQ_PS_MIO7/VM0: J1.40, R75.2, U2.D5 (PS_MIO7_500)
ZYNQ_PS_MIO8\VM1: J1.36, R74.1, U2.E5 (PS_MIO8_500)
ZYNQ_PS_MIO9: J1.52, U2.C4 (PS_MIO9_500)
ZYNQ_PS_MIO10: J1.42, U2.G7 (PS_MIO10_500)
ZYNQ_PS_MIO11: J1.48, U2.B4 (PS_MIO11_500)
ZYNQ_PS_MIO12: J1.46, U2.C5 (PS_MIO12_500)
ZYNQ_PS_MIO13: U2.A6 (PS_MIO13_500), U9.27 (PB14)
ZYNQ_PS_POR: R100.2, U2.B5 (PS_POR_B_500), U9.25 (PB12)
ZYNQ_PS_SRST: R94.2, TP5.1, U2.C9 (PS_SRST_B_501), U9.26 (PB13)
ZYNQ_TCK: J1.64, U2.G11 (TCK_0)
ZYNQ_TDI: J1.70, U2.H13 (TDI_0)
ZYNQ_TDO: J1.68, U2.G14 (TDO_0)
ZYNQ_TMS: J1.66, U2.G12 (TMS_0)
eMMC_CLK: U2.D11 (PS_MIO48_501), U7.M6 (CLK)
eMMC_CMD: R39.2, U2.B10 (PS_MIO47_501), U7.M5 (CMD)
eMMC_D0: R40.2, U2.D12 (PS_MIO46_501), U7.A3 (DAT0)
eMMC_D1: R41.2, U2.C14 (PS_MIO49_501), U7.A4 (DAT1)
eMMC_D2: R42.2, U2.D13 (PS_MIO50_501), U7.A5 (DAT2)
eMMC_D3: R43.2, U2.C10 (PS_MIO51_501), U7.B2 (DAT3)
eMMC_~RST: R97.2, U7.K5 (~RST), U9.16 (PC4)
